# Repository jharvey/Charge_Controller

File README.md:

# FUGU-ARDUINO-MPPT-HARDWARE-KICAD
An open source Arduino ESP32 MPPT Solar Charge Controller firmware equipped with charging algorithms, WiFi, LCD menus &amp; more!
Stay tuned for the design release and video tutorial.<br>

Orginal Firmware project found here https://github.com/AngeloCasi/FUGU-ARDUINO-MPPT-FIRMWARE<br>
Oringal Hardware project found here https://drive.google.com/drive/folders/1Sd2jWAb-F8NAXlJ6PLdhcnPDQV0alD15?usp=sharing<br>

<div align="center">

<div align="left">
OnShape 3D found here https://cad.onshape.com/documents/5882843f0ee96e62ba8b9faf/w/820f02cb3842ce32ae850702/e/1fe43df2095ddf6be5cc563b?renderMode=0&uiState=630a19a00173156e6a7194ef<br>
GPL open-source DIY Charge Controller<br>

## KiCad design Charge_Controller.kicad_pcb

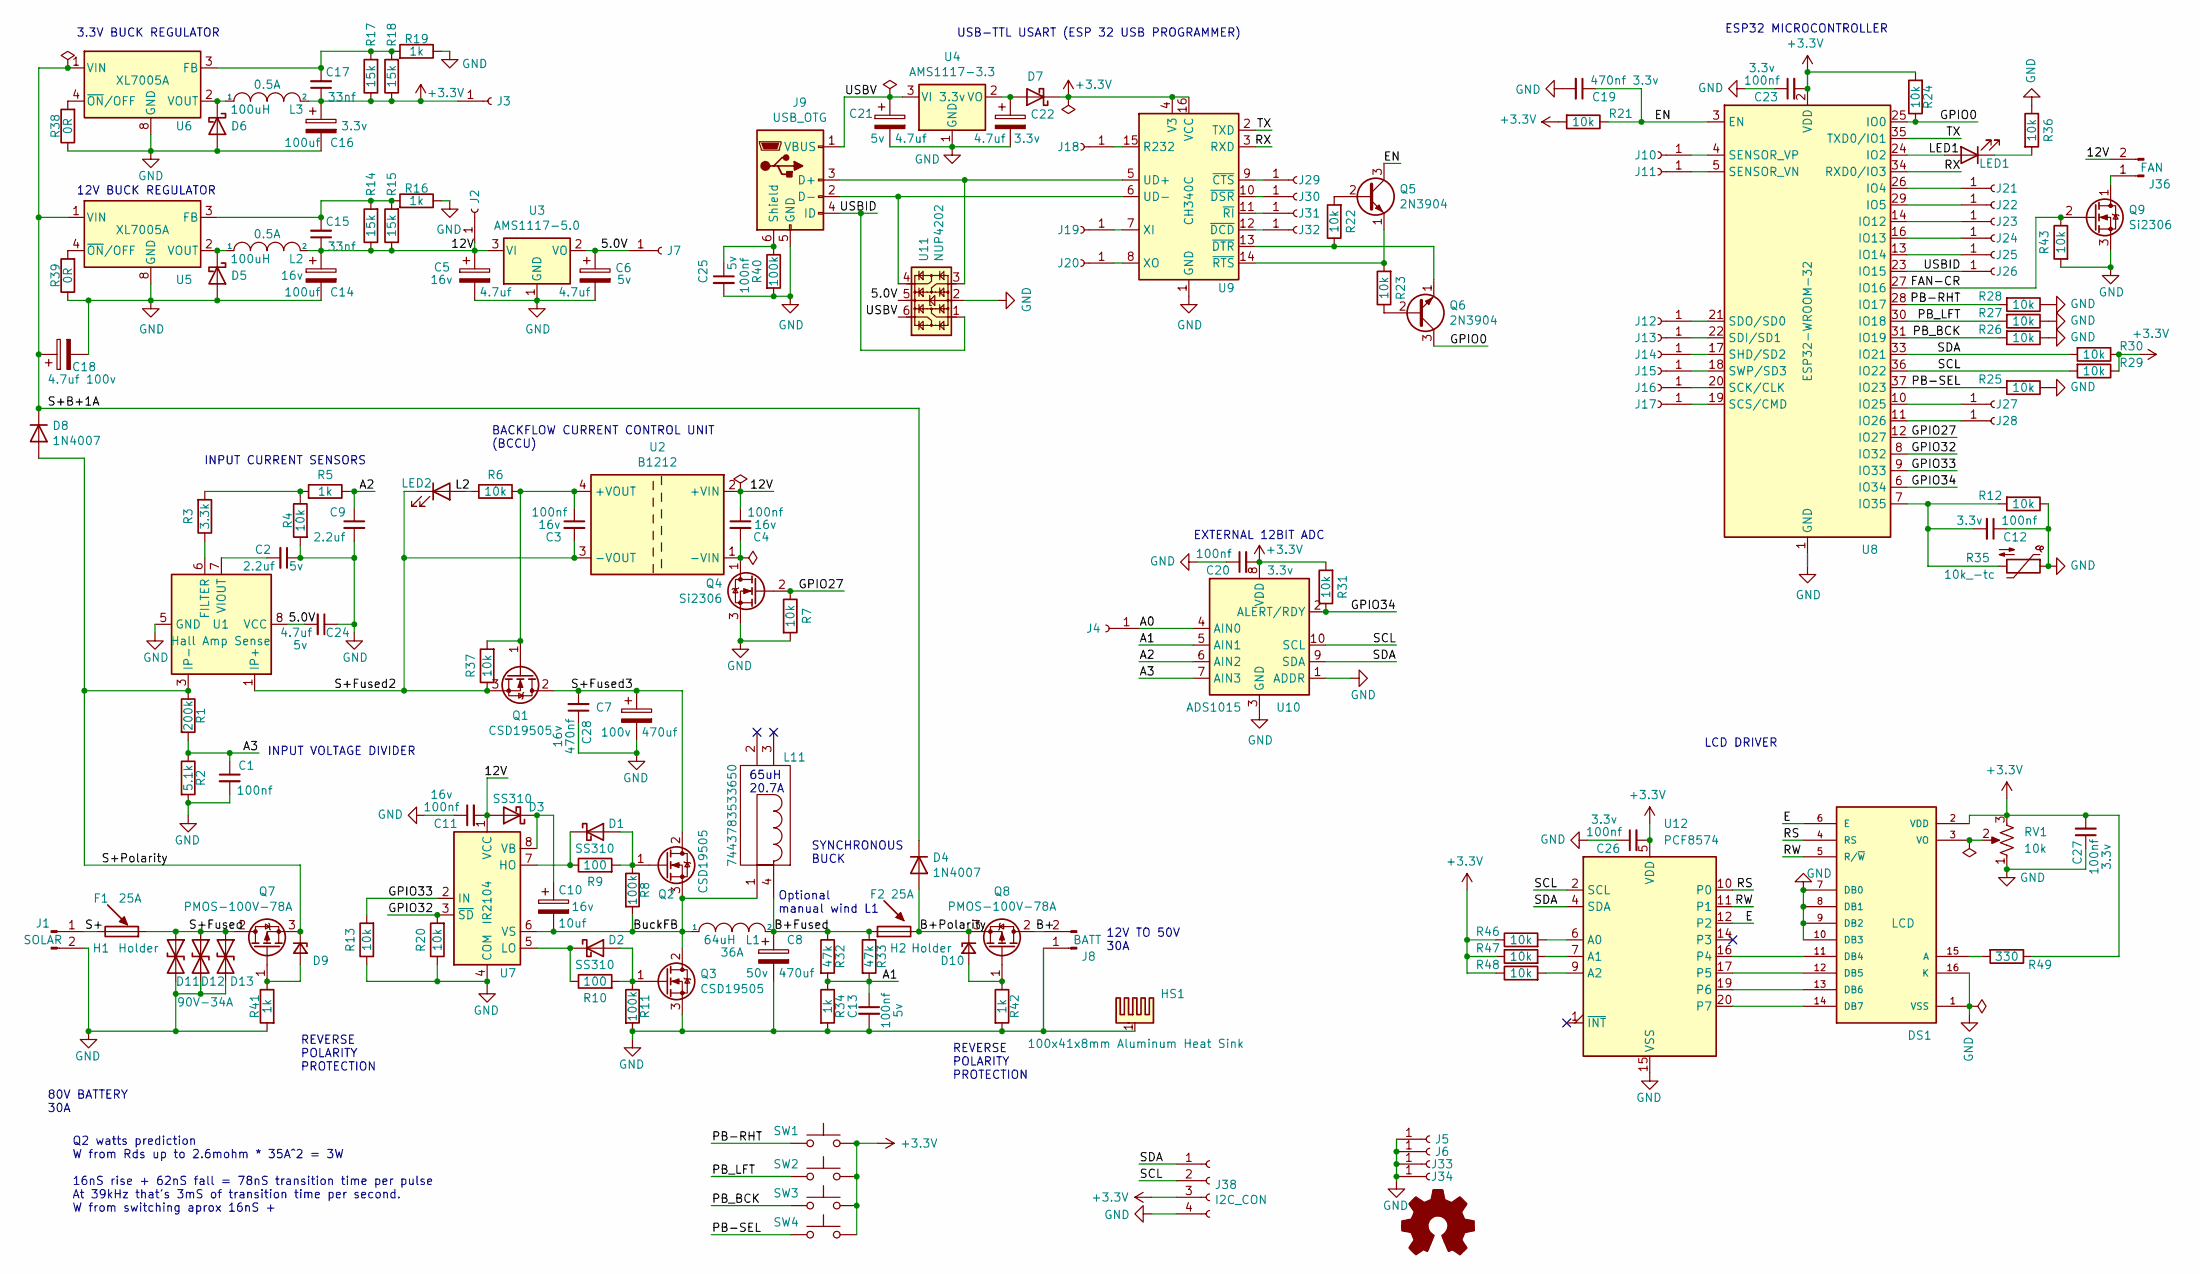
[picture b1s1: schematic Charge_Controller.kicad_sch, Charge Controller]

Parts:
C1, C3, C4, C11, C12, C13, C20, C23, C25, C26, C27: 100nf; C_0805_2012Metric; LCSC C28233
C2, C9: 2.2uf; C_0805_2012Metric; LCSC C49217
C5, C6, C21, C22, C24: 4.7uf; C_0805_2012Metric; LCSC C1779
C7, C8: 470uf; CP_Radial_D16.0mm_P7.50mm; LCSC C513392
C10: 10uf; C_0805_2012Metric; LCSC C15850
C14, C16: 100uf; CP_Elec_8x10; LCSC C445063
C15, C17: 33nf; C_0805_2012Metric; LCSC C53175
C18: 4.7uf; CP_Radial_D10.0mm_P5.00mm; Digikey 399-ESH107M100AH4AA-ND
C19, C28: 470nf; C_0805_2012Metric; LCSC C13967
D1, D2, D3, D5, D6, D7: SS310; D_SMA; LCSC C15874
D4, D8: 1N4007; D_SMA; LCSC C727081
D9, D10: D_Zener_Small; D_MiniMELF; LCSC C8062
D11, D12, D13: 90V-34A; D_SMC-RM10_Universal_Handsoldering; LCSC C2912801
DS1: LCD; LCD_LCM-S01602DTR_A; Digikey 3387-ACM1602K-NLW-BBW-ND
F1, F2: 25A; ESD-Logo_6.6x6mm_SilkScreen; LCSC C116701
H1, H2: Holder; Fuse_Blade_C2935871; LCSC C2935871
HS1: 100x41x8mm Aluminum Heat Sink; MountingHole_2.5mm_Pad_Via; Digikey NA
J1: SOLAR; TerminalBlock_MetzConnect_Type703_RT10N02HGLU_1x02_P9.52mm_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; LCSC C92145
J2, J3, J4, J5, J6, J7, J10, J11, J12, J13, J14, J15, J16, J17, J18, J19, J20, J21, J22, J23, J24, J25, J26, J27, J28, J29, J30, J31, J32: Conn_01x01_Female; TestPoint_Loop_D3.50mm_Drill0.9mm_Beaded; LCSC NA
J8: BATT; TerminalBlock_MetzConnect_Type703_RT10N02HGLU_1x02_P9.52mm_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; LCSC C92145
J9: USB_OTG; USB_Micro-AB_Molex_47590-0001; LCSC C136001
J33, J34: Conn_01x01_Female; MountingHole_2.5mm_Pad_Via; LCSC NA
J36: FAN; TerminalBlock_MetzConnect_Type703_RT10N02HGLU_1x02_P9.52mm_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; LCSC C92145
J38: I2C_CON; PinHeader_1x04_P2.54mm_Vertical; LCSC NA
L1: 64uH; L_Axial_L30.0mm_D8.0mm_P35.56mm_Horizontal_Fastron_77A; LCSC NA
L2, L3: 100uH; L_Taiyo-Yuden_NR-60xx_HandSoldering; LCSC C88132
L11: 7443783533650; Digikey 732-13654-ND
LED1, LED2: LED; LED_0805_2012Metric; LCSC C84256
LOGO1: Logo_Open_Hardware_Small; OSHW-Symbol_6.7x6mm_SilkScreen; LCSC NA
Q1, Q2, Q3: CSD19505; TO-263-2; LCSC C485534
Q4, Q9: Si2306; SOT-23; LCSC C347489
Q5, Q6: 2N3904; SOT-23; LCSC C18536
Q7, Q8: PMOS-100V-78A; TO-252-2; LCSC C216784
R1: 200k; R_0805_2012Metric; LCSC C17539
R2: 5.1k; R_0805_2012Metric; LCSC C27834
R3: 3.3k; R_0805_2012Metric; LCSC C26010
R4, R6, R7, R12, R13, R20, R21, R22, R23, R24, R25, R26, R27, R28, R29, R30, R31, R36, R37, R43, R46, R47, R48: 10k; R_0805_2012Metric; LCSC C17724
R5, R16, R19, R34, R41, R42: 1k; R_0805_2012Metric; LCSC C17513
R8, R11, R40: 100k; R_0805_2012Metric; LCSC C149504
R9, R10: 100; R_0805_2012Metric; LCSC C17408
R14, R15, R17, R18: 15k; R_0805_2012Metric; LCSC C17475
R32, R33: 47k; R_0805_2012Metric; LCSC C17713
R35: 10k_-tc; PinHeader_1x02_P2.54mm_Vertical; Digikey BC2380-ND
R38, R39: 0R; R_0603_1608Metric; LCSC C21189
R49: 330; R_0805_2012Metric; LCSC C17630
RV1: 10k; Potentiometer_Bourns_3314G_Vertical; LCSC C780220
SW1: RIGHT; SW_SPST_EVQQ2; LCSC C318884
SW2: LEFT; SW_SPST_EVQQ2; LCSC C318884
SW3: BACK; SW_SPST_EVQQ2; LCSC C318884
SW4: SELECT; SW_SPST_EVQQ2; LCSC C318884
U1: Hall Amp Sense; SOIC-8_3.9x4.9mm_P1.27mm; LCSC C2930869
U2: B1212; Converter_DCDC_muRata_CRE1xxxxxxSC_THT; LCSC C5127060
U3: AMS1117-5.0; SOT-223-3_TabPin2; LCSC C6187
U4: AMS1117-3.3; SOT-223-3_TabPin2; LCSC C6186
U5, U6: XL7005A; SOIC-8_3.9x4.9mm_P1.27mm; LCSC C50848
U7: IR2104; SOIC-8_3.9x4.9mm_P1.27mm; LCSC C2960
U8: ESP32-WROOM-32; LCSC C701343
U9: CH340C; STC_SOP-16_3.9x9.9mm_P1.27mm; LCSC C84681
U10: ADS1015; TSSOP-10_3x3mm_P0.5mm; LCSC C193969
U11: NUP4202; SOT-363_SC-70-6; LCSC C89319
U12: PCF8574; SSOP-20_5.3x7.2mm_P0.65mm; LCSC C57790

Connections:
+3.3VA: C16.1, C17.1, C20.2, C23.2, C26.2, C27.2, D7.1 (K), DS1.2 (VDD), J3.1, J38.3, L3.2, R17.1, R18.1, R21.2, R24.2, R29.1, R30.1, R31.2, R46.1, R47.1, R48.1, R49.1, RV1.3, SW1.2, SW2.2, SW3.2, SW4.2, U8.2 (VDD), U9.4 (V3), U9.16 (VCC), U10.8 (VDD), U12.5 (VDD)
/5.0V: C6.1, C24.2, J7.1, U1.8 (VCC), U3.2 (VO), U11.5
/12V: C4.1, C5.1, C11.2, C14.1, C15.1, D3.2 (A), J2.1, J36.2, L2.2, R14.1, R15.1, U2.2 (+VIN), U3.3 (VI), U7.1 (VCC)
/A0: J4.1, U10.4 (AIN0)
/A1: C13.1, R32.2, R33.2, R34.1, U10.5 (AIN1)
/A2: C9.1, R5.1, U10.6 (AIN2)
/A3: C1.1, R1.2, R2.1, U10.7 (AIN3)
/B+: J8.2, Q8.2 (D)
/B+Fused: C8.1, H2.2, L1.2, L11.4, R32.1, R33.1
/B+Polarity: D4.2 (A), D10.1 (K), H2.1, Q8.3 (S)
/BuckFB: C10.2, L1.1, L11.1, Q2.3 (S), Q3.2 (D), R8.2, U7.6 (VS)
/E: DS1.6 (E), U12.12 (P2)
/EN: C19.1, Q5.3 (C), R21.1, U8.3 (EN)
/FAN-CR: Q9.2 (G), R43.1, U8.27 (IO16)
/GPIO0: Q6.3 (C), R24.1, U8.25 (IO0)
/GPIO27: Q4.2 (G), R7.1, U8.12 (IO27)
/GPIO32: R20.2, U7.3 (~SD), U8.8 (IO32)
/GPIO33: R13.2, U7.2 (IN), U8.9 (IO33)
/GPIO34: R31.1, U8.6 (IO34), U10.2 (ALERT/RDY)
/L2: LED2.2 (A), R6.1
/LED1: LED1.2 (A), U8.24 (IO2)
/PB-RHT: R28.2, SW1.1, U8.28 (IO17)
/PB-SEL: R25.2, SW4.1, U8.37 (IO23)
/PB_BCK: R26.2, SW3.1, U8.31 (IO19)
/PB_LFT: R27.2, SW2.1, U8.30 (IO18)
/RS: DS1.4 (RS), U12.10 (P0)
/RW: DS1.5 (R/~W), U12.11 (P1)
/RX: U8.34 (RXD0/IO3), U9.3 (RXD)
/S+: H1.1, J1.1
/S+B+1A: C18.1, D4.1 (K), D8.1 (K), U5.1 (VIN), U6.1 (VIN)
/S+Fused: D11.1 (A1), D12.1 (A1), D13.1 (A1), H1.2, Q7.2 (D)
/S+Fused2: C3.2, LED2.1 (K), Q1.3 (S), R37.1, U1.1 (IP+), U1.2 (IP+), U2.3 (-VOUT)
/S+Fused3: C7.1, C28.2, Q1.2 (D), Q2.2 (D)
/S+Polarity: D8.2 (A), D9.1 (K), Q7.3 (S), R1.1, U1.3 (IP-), U1.4 (IP-)
/SCL: J38.2, R29.2, U8.36 (IO22), U10.10 (SCL), U12.2 (SCL)
/SDA: J38.1, R30.2, U8.33 (IO21), U10.9 (SDA), U12.4 (SDA)
/TX: U8.35 (TXD0/IO1), U9.2 (TXD)
/USBID: J9.4 (ID), J26.1, U8.23 (IO15), U11.1
/USBV: C21.1, J9.1 (VBUS), U4.3 (VI), U11.6
GND: C1.2, C2.1, C5.2, C6.2, C7.2, C8.2, C9.2, C11.1, C12.1, C13.2, C14.2, C16.2, C18.2, C19.2, C20.1, C21.2, C22.2, C23.1, C24.1, C25.2, C26.1, C27.1, C28.1, D5.2 (A), D6.2 (A), D11.2 (A2), D12.2 (A2), D13.2 (A2), DS1.1 (VSS), DS1.7 (DB0), DS1.8 (DB1), DS1.9 (DB2), DS1.10 (DB3), DS1.16 (K), HS1.1, J1.2, J5.1, J6.1, J8.1, J9.5 (GND), J33.1, J34.1, J38.4, Q3.3 (S), Q4.3 (S), Q9.3 (S), R2.2, R4.2, R7.2, R11.2, R12.1, R13.1, R16.1, R19.1, R20.1, R25.1, R26.1, R27.1, R28.1, R34.2, R35.1, R36.1, R38.1, R39.1, R40.2, R41.2, R42.2, R43.2, RV1.1, U1.5 (GND), U3.1 (GND), U4.1 (GND), U5.5 (GND), U5.6 (GND), U5.7 (GND), U5.8 (GND), U6.5 (GND), U6.6 (GND), U6.7 (GND), U6.8 (GND), U7.4 (COM), U8.1 (GND), U8.15 (GND), U8.38 (GND), U8.39 (GND), U9.1 (GND), U10.1 (ADDR), U10.3 (GND), U11.2, U12.15 (VSS)
unnamed: C2.2, U1.7 (VIOUT)
unnamed: C3.1, Q1.1 (G), R6.2, R37.2, U2.4 (+VOUT)
unnamed: C4.2, Q4.1 (D), U2.1 (-VIN)
unnamed: C10.1, D3.1 (K), U7.8 (VB)
unnamed: C12.2, R12.2, R35.2, U8.7 (IO35)
unnamed: C15.2, R14.2, R15.2, R16.2, U5.3 (FB)
unnamed: C17.2, R17.2, R18.2, R19.2, U6.3 (FB)
unnamed: C22.1, D7.2 (A), U4.2 (VO)
unnamed: C25.1, J9.6 (Shield), R40.1
unnamed: D1.1 (K), R9.1, U7.7 (HO)
unnamed: D1.2 (A), Q2.1 (G), R8.1, R9.2
unnamed: D2.1 (K), R10.1, U7.5 (LO)
unnamed: D2.2 (A), Q3.1 (G), R10.2, R11.1
unnamed: D5.1 (K), L2.1, U5.2 (VOUT)
unnamed: D6.1 (K), L3.1, U6.2 (VOUT)
unnamed: D9.2 (A), Q7.1 (G), R41.1
unnamed: D10.2 (A), Q8.1 (G), R42.1
unnamed: DS1.3 (VO), RV1.2
unnamed: DS1.11 (DB4), U12.16 (P4)
unnamed: DS1.12 (DB5), U12.17 (P5)
unnamed: DS1.13 (DB6), U12.19 (P6)
unnamed: DS1.14 (DB7), U12.20 (P7)
unnamed: DS1.15 (A), R49.2
unnamed: J9.2 (D-), U9.6 (UD-), U11.4
unnamed: J9.3 (D+), U9.5 (UD+), U11.3
unnamed: J10.1, U8.4 (SENSOR_VP)
unnamed: J11.1, U8.5 (SENSOR_VN)
unnamed: J12.1, U8.21 (SDO/SD0)
unnamed: J13.1, U8.22 (SDI/SD1)
unnamed: J14.1, U8.17 (SHD/SD2)
unnamed: J15.1, U8.18 (SWP/SD3)
unnamed: J16.1, U8.20 (SCK/CLK)
unnamed: J17.1, U8.19 (SCS/CMD)
unnamed: J18.1, U9.15 (R232)
unnamed: J19.1, U9.7 (XI)
unnamed: J20.1, U9.8 (XO)
unnamed: J21.1, U8.26 (IO4)
unnamed: J22.1, U8.29 (IO5)
unnamed: J23.1, U8.14 (IO12)
unnamed: J24.1, U8.16 (IO13)
unnamed: J25.1, U8.13 (IO14)
unnamed: J27.1, U8.10 (IO25)
unnamed: J28.1, U8.11 (IO26)
unnamed: J29.1, U9.9 (~CTS)
unnamed: J30.1, U9.10 (~DSR)
unnamed: J31.1, U9.11 (~RI)
unnamed: J32.1, U9.12 (~DCD)
unnamed: LED1.1 (K), R36.2
unnamed: Q5.1 (E), R23.2, U9.14 (~RTS)
unnamed: Q5.2 (B), R22.2
unnamed: Q6.1 (E), R22.1, U9.13 (~DTR)
unnamed: Q6.2 (B), R23.1
unnamed: J36.1, Q9.1 (D)
unnamed: R3.1, U1.6 (FILTER)
unnamed: R3.2, R4.1, R5.2
unnamed: R38.2, U6.4 (~ON/OFF)
unnamed: R39.2, U5.4 (~ON/OFF)
unnamed: R46.2, U12.6 (A0)
unnamed: R47.2, U12.7 (A1)
unnamed: R48.2, U12.9 (A2)

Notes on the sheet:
SYNCHRONOUS BUCK
3.3V BUCK REGULATOR
USB-TTL USART (ESP 32 USB PROGRAMMER)
Optional manual wind L1
BACKFLOW CURRENT CONTROL UNIT (BCCU)
65uH 20.7A
12V BUCK REGULATOR
80V BATTERY 30A
INPUT CURRENT SENSORS
REVERSE POLARITY PROTECTION
Q2 watts prediction W from Rds up to 2.6mohm * 35A^2 = 3W 16nS rise + 62nS fall = 78nS transition time per pulse At 39kHz that's 3mS of transition time per second. W from switching aprox 16nS +
LCD DRIVER
INPUT VOLTAGE DIVIDER
12V TO 50V 30A
ESP32 MICROCONTROLLER
EXTERNAL 12BIT ADC

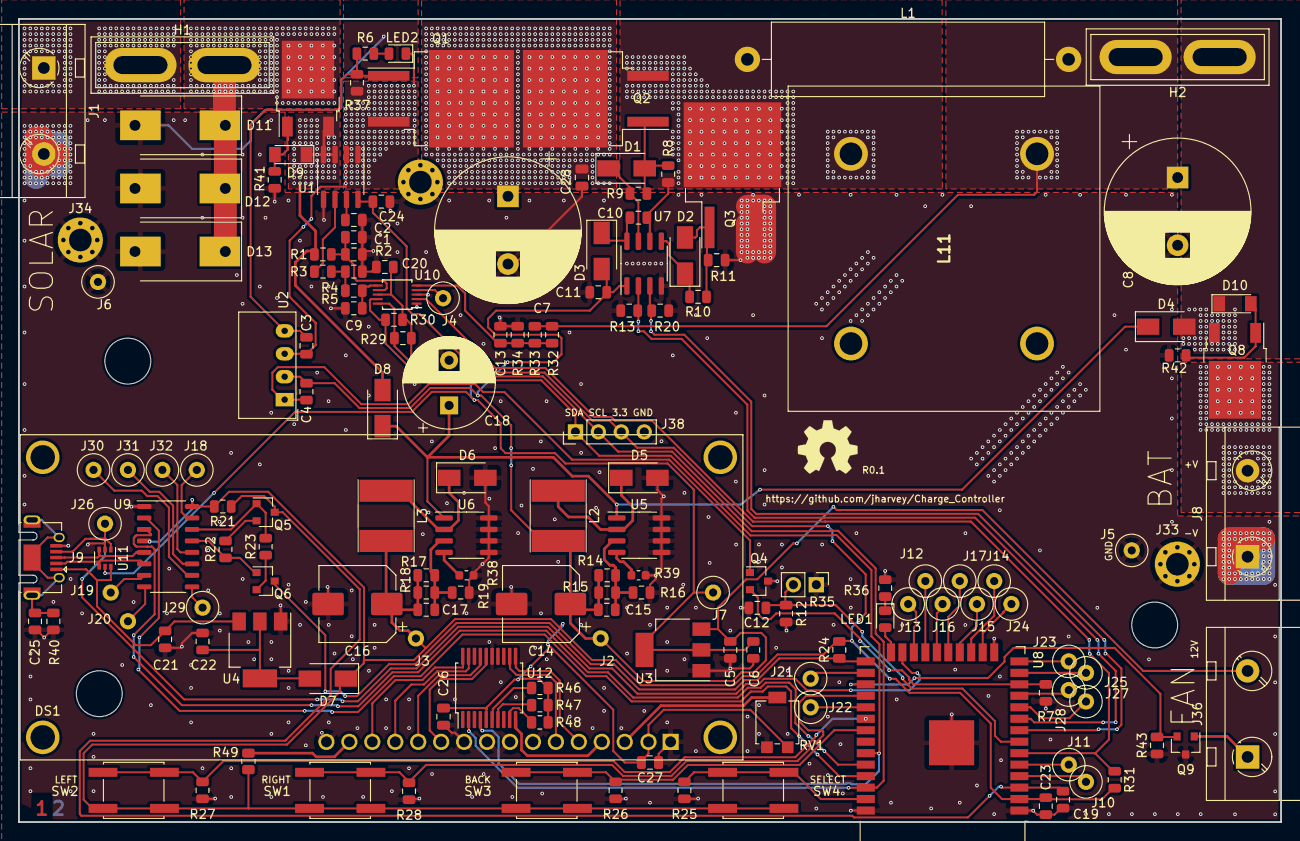
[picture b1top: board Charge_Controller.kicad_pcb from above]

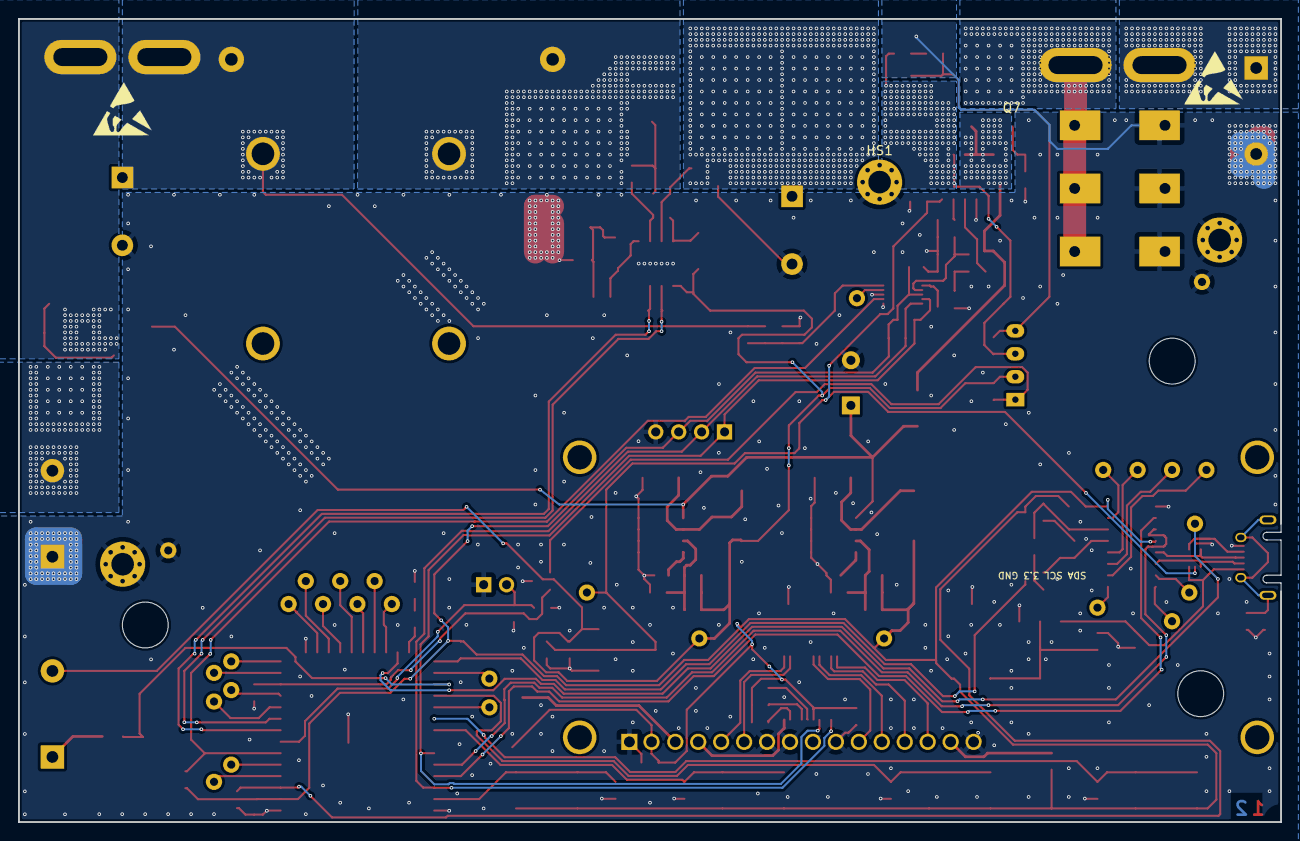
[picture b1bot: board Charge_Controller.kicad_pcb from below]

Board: 2 copper layers, 139.7 x 88.9 mm, 163 parts (3 on the bottom side), 100 nets.

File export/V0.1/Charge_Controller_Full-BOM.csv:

Comment,Designator,Footprint,LCSC
"100nf","C1,C3,C4,C11,C12,C13,C20,C23,C25,C26,C27","Capacitor_SMD:C_0805_2012Metric","C28233"
"10uf","C10","Capacitor_SMD:C_0805_2012Metric","C15850"
"100uf","C14,C16","Capacitor_SMD:CP_Elec_8x10","C445063"
"33nf","C15,C17","Capacitor_SMD:C_0805_2012Metric","C53175"
"4.7uf","C18","Capacitor_THT:CP_Radial_D10.0mm_P5.00mm","C503212"
"470nf","C19,C28","Capacitor_SMD:C_0805_2012Metric","C13967"
"2.2uf","C2,C9","Capacitor_SMD:C_0805_2012Metric","C49217"
"4.7uf","C5,C6,C21,C22,C24","Capacitor_SMD:C_0805_2012Metric","C1779"
"470uf","C7,C8","Capacitor_THT:CP_Radial_D16.0mm_P7.50mm","C513392"
"SS310","D1,D2,D3,D5,D6,D7","Diode_SMD:D_SMA","C15874"
"90V-34A","D11,D12,D13","Diode_SMD:D_SMC-RM10_Universal_Handsoldering","C2912801"
"1N4007","D4,D8","Diode_SMD:D_SMA","C727081"
"D_Zener_Small","D9,D10","Diode_SMD:D_MiniMELF","C8062"
"LCD","DS1","LCD:LCD_LCM-S01602DTR_A","C83275"
"25A","F1,F2","Symbol:ESD-Logo_6.6x6mm_SilkScreen","C116701"
"Holder","H1,H2","Fuse_Holder:Fuse_Blade_C2935871","C2935871"
"100x41x8mm Aluminum Heat Sink","HS1","MountingHole:MountingHole_2.5mm_Pad_Via","NA"
"SOLAR","J1","TerminalBlock_MetzConnect:TerminalBlock_MetzConnect_Type703_RT10N02HGLU_1x02_P9.52mm_Horizontal","C92145"
"Conn_01x01_Female","J2,J3,J4,J5,J6,J7,J10,J11,J12,J13,J14,J15,J16,J17,J18,J19,J20,J21,J22,J23,J24,J25,J26,J27,J28,J29,J30,J31,J32","TestPoint:TestPoint_Loop_D3.50mm_Drill0.9mm_Beaded","NA"
"Conn_01x01_Female","J33,J34","MountingHole:MountingHole_2.5mm_Pad_Via","NA"
"FAN","J36","TerminalBlock_MetzConnect:TerminalBlock_MetzConnect_Type703_RT10N02HGLU_1x02_P9.52mm_Horizontal","C92145"
"I2C_CON","J38","Connector_PinHeader_2.54mm:PinHeader_1x04_P2.54mm_Vertical","NA"
"BATT","J8","TerminalBlock_MetzConnect:TerminalBlock_MetzConnect_Type703_RT10N02HGLU_1x02_P9.52mm_Horizontal","C92145"
"USB_OTG","J9","Connector_USB:USB_Micro-AB_Molex_47590-0001","C136001"
"64uH","L1","Inductor_THT:L_Axial_L30.0mm_D8.0mm_P35.56mm_Horizontal_Fastron_77A","NA"
"7443783533650","L11","7443783533650_inductor:7443783533650","NA"
"100uH","L2,L3","Inductor_SMD:L_Taiyo-Yuden_NR-60xx_HandSoldering","C88132"
"LED","LED1,LED2","LED_SMD:LED_0805_2012Metric","C84256"
"Logo_Open_Hardware_Small","LOGO1","Symbol:OSHW-Symbol_6.7x6mm_SilkScreen","NA"
"CSD19505","Q1,Q2,Q3","Package_TO_SOT_SMD:TO-263-2","C485534"
"Si2306","Q4,Q9","Package_TO_SOT_SMD:SOT-23","C347489"
"2N3904","Q5,Q6","Package_TO_SOT_SMD:SOT-23","C18536"
"PMOS-100V-78A","Q7,Q8","Package_TO_SOT_SMD:TO-252-2","C216784"
"200k","R1","Resistor_SMD:R_0805_2012Metric","C17539"
"15k","R14,R15,R17,R18","Resistor_SMD:R_0805_2012Metric","C17475"
"5.1k","R2","Resistor_SMD:R_0805_2012Metric","C27834"
"3.3k","R3","Resistor_SMD:R_0805_2012Metric","C26010"
"47k","R32,R33","Resistor_SMD:R_0805_2012Metric","C17713"
"10k_-tc","R35","Connector_PinHeader_2.54mm:PinHeader_1x02_P2.54mm_Vertical","NA"
"0R","R38,R39","Resistor_SMD:R_0603_1608Metric","C21189"
"10k","R4,R6,R7,R12,R13,R20,R21,R22,R23,R24,R25,R26,R27,R28,R29,R30,R31,R36,R37,R43,R46,R47,R48","Resistor_SMD:R_0805_2012Metric","C17724"
"330","R49","Resistor_SMD:R_0805_2012Metric","C17630"
"1k","R5,R16,R19,R34,R41,R42","Resistor_SMD:R_0805_2012Metric","C17513"
"100k","R8,R11,R40","Resistor_SMD:R_0805_2012Metric","C149504"
"100","R9,R10","Resistor_SMD:R_0805_2012Metric","C17408"
"10k","RV1","Potentiometer_SMD:Potentiometer_Bourns_3314G_Vertical","C780220"
"RIGHT","SW1","Button_Switch_SMD:SW_SPST_EVQQ2","C318884"
"LEFT","SW2","Button_Switch_SMD:SW_SPST_EVQQ2","C318884"
"BACK","SW3","Button_Switch_SMD:SW_SPST_EVQQ2","C318884"
"SELECT","SW4","Button_Switch_SMD:SW_SPST_EVQQ2","C318884"
"Hall Amp Sense","U1","Package_SO:SOIC-8_3.9x4.9mm_P1.27mm","C2930869"
"ADS1015","U10","Package_SO:TSSOP-10_3x3mm_P0.5mm","C193969"
"NUP4202","U11","Package_TO_SOT_SMD:SOT-363_SC-70-6","C89319"
"PCF8574","U12","Package_SO:SSOP-20_5.3x7.2mm_P0.65mm","C57790"
"B1212","U2","Converter_DCDC:Converter_DCDC_muRata_CRE1xxxxxxSC_THT","C5127060"
"AMS1117-5.0","U3","Package_TO_SOT_SMD:SOT-223-3_TabPin2","C6187"
"AMS1117-3.3","U4","Package_TO_SOT_SMD:SOT-223-3_TabPin2","C6186"
"XL7005A","U5,U6","Package_SO:SOIC-8_3.9x4.9mm_P1.27mm","C50848"
"IR2104","U7","Package_SO:SOIC-8_3.9x4.9mm_P1.27mm","C2960"
"ESP32-WROOM-32","U8","RF_Module:ESP32-WROOM-32","C701343"
"CH340C","U9","Package_SO:STC_SOP-16_3.9x9.9mm_P1.27mm","C84681"


Comment,na,na,McMaster
Passivated 18-8 Stainless Steel Phillips Flat Head Screw 82 Degree Countersink 2-56 Thread 1-1/2" Long,,,91771A267
Passivated 18-8 Stainless Steel Phillips Flat Head Screw 82 Degree Countersink 2-56 Thread 1-1/2" Long,,,91771A267
Passivated 18-8 Stainless Steel Phillips Flat Head Screw 82 Degree Countersink 2-56 Thread 1-1/2" Long,,,91771A267
Passivated 18-8 Stainless Steel Phillips Flat Head Screw 82 Degree Countersink 2-56 Thread 1-1/2" Long,,,91771A267
316 Stainless Steel Washer for Number 2 Screw Size 0.094" ID 0.25" OD,,,90107A003
316 Stainless Steel Washer for Number 2 Screw Size 0.094" ID 0.25" OD,,,90107A003
316 Stainless Steel Washer for Number 2 Screw Size 0.094" ID 0.25" OD,,,90107A003
316 Stainless Steel Washer for Number 2 Screw Size 0.094" ID 0.25" OD,,,90107A003
18-8 Stainless Steel Nylon-Insert Locknut 2-56 Thread Size,,,91831A002
18-8 Stainless Steel Nylon-Insert Locknut 2-56 Thread Size,,,91831A002
18-8 Stainless Steel Nylon-Insert Locknut 2-56 Thread Size,,,91831A002
18-8 Stainless Steel Nylon-Insert Locknut 2-56 Thread Size,,,91831A002
Off-White Nylon Unthreaded Spacer 1/4" OD 1" Long for Number 2 Screw Size,,,94639A198
Off-White Nylon Unthreaded Spacer 1/4" OD 1" Long for Number 2 Screw Size,,,94639A198
Off-White Nylon Unthreaded Spacer 1/4" OD 1" Long for Number 2 Screw Size,,,94639A198
Off-White Nylon Unthreaded Spacer 1/4" OD 1" Long for Number 2 Screw Size,,,94639A198
Zinc-Plated Steel Phillips Flat Head Screws 82 Degree Countersink Angle 4-40 Thread Size 5/8" Long,,,90273A112
Zinc-Plated Steel Phillips Flat Head Screws 82 Degree Countersink Angle 4-40 Thread Size 5/8" Long,,,90273A112


3D printed base enclosure
3D printed top enclosure
3D printed push button extenders

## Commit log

2022-08-14 Initial Schematic capture DRAFT
2022-08-14 Updated the README.md to reflect this project.
2022-08-14 Draft BOM, ADDED surge and reverse polarity protection U11, Q7, Q8
2022-08-15 Aligned footprints with JLPCB rotations and offsets, deleted some JLCPCB automation files.
2022-08-15 Added FAN controller circuit
2022-08-16 Added push buttons, LCD connector, and fan MOSFET to schematic.
2022-08-17 Started layout of PCB, first grouping of components.
2022-08-20 Initial draft layout, no traces yet, but parts are mostly arranged.
2022-08-20 More PCB initial setup, 2oz copper, widths, via's etc.
2022-08-20 Converted to KCAD 6, more draft layout.
2022-08-21 Another incremental layout draft.
2022-08-22 Draft, no more courtyard problems, all traces connected
2022-08-22 Not sure why these were not part of the repo, adding them now. Oops.
2022-08-23 Draft adding I2C to LCD driver.
2022-08-26 R0.1 almost done draft.
2022-08-26 Added a bit of silk screen.
2022-08-26 Added step file and png graphic to repo.
2022-08-26 Attempting to add picture to README.md
2022-08-27 changed some wrl's to step files, Made 3D case for PCB via OnShape
2022-08-27 Updated 3D picture, updated README.md to include this graphic.
2022-08-27 Format change
2022-08-27 Attempting to export a BOM, save before doing something potentially risky.
2022-08-27 Potentially going to release this as the first spin.
2022-08-28 Added a Digikey number for the toroid.
2022-08-28 Added link and note to original hardware files.
2022-08-28 Update README.md
    Format changes to links of the original work.
2022-08-28 Deleted extra old project file. I'm not sure why I had 2 files / this old scrap file.
2022-08-28 git Ignore the backup folders contents.
2022-09-05 Moved C7 to other side of current sensor, changed C7 and C8 from Axial to Radial, moved U3 slightly. https://github.com/jharvey/Charge_Controller/issues/2
2022-09-05 Added D11, D12 and D13 for input surge protection. https://github.com/jharvey/Charge_Controller/issues/3
2022-09-05 Changed the hall sensor and added some notes.
2022-09-07 Initial simulation for Q1 and Q2 MOSFET heat
2022-09-08 Small progress on heat sim. This model shows KA of current from the MOSFET's. Looks like I'll have to use the file based voltage control instead of the generic pulse power supplies. \https://github.c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
2022-09-09 Added simulation graphic.
2022-09-09 updated simulation graphic
2022-09-09 Left click when you click the text of the graph, will integrate and report. New picture added to show the energy in 10mS period of time.
2022-09-09 Created PWL bases simulation, and made heat predictions.
2022-09-11 Heat load simulation at 12A steady state. Added several simulations, including CSD17510Q5A.spice.mod imported from the PSPICE for TI model.
2022-09-11 Added more pictures of specific volts, amps, etc. Pictures showing key simulation items.
2022-09-11 Renamed file, added another documentation picture.
2022-09-20 Draft layout, still needs a bunch, but everything is connected.
2022-09-20 Peppered it with via's, silk screen is probably good a this point. Almost ready for a review.
2022-09-22 R0.1 ready for review
2022-09-23 Added some documentation for thermal via predictions and buck regulator design.
2022-09-24 Updated Q2 and Q3 watts prediction note on schematic. It now notes the spice simulation prediction watts.
2022-09-24 Updated mechanical drawing of the final enclosure.
2022-09-24 Corrected typo in PDF file name.
2022-09-24 Updated picture, now includes misc hardware for LCD.
